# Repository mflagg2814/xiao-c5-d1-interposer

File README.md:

# XIAO ESP32-C5 to Wemos D1 mini interposer

> [!IMPORTANT]
> V1.0 hasn't been built or tested yet.\
> Use it at your own risk and without expectation of support.

A small interposer that lets a surface-mounted [Seeed Studio XIAO ESP32-C5](https://wiki.seeedstudio.com/xiao_esp32c5_getting_started/) stand in for a Wemos D1 mini (ESP8266). It breaks the XIAO out to the D1 mini's two 1×8 rows with the D1 mini's pin spacing, so it drops into D1 mini sockets and takes D1 mini shields.

It was built for the [AirGradient DIY Basic](https://www.airgradient.com/documentation/kb/kb-old-instructions-the-airgradient-diy-air-quality-sensor-basic-version-pcb-version-3-0). The pin map also aims to keep the board useful as a general D1 mini replacement.

Schematic: [c5-d1-interposer-schematic.pdf](c5-d1-interposer-schematic.pdf) (source: `c5-d1-interposer.kicad_sch`)

### AI disclosure

AI was used to generate this PCB with human guidance and revision. Provided without support.

## Fabrication

I had 3 of these fabbed 11/2026 at OSH Park for $4.05 including shipping. I went with 2oz copper, 0.8mm thickness.

## SHT3x: rewire VIN to 3.3 V

> [!WARNING]
> The SHT3x's VIN trace must be cut and rewired to 3.3 V before the XIAO goes in.

The AirGradient board powers the SHT3x module from 5 V. If that module has its own I2C pull-ups to VIN, SDA and SCL idle above the C5's 3.6 V absolute maximum. With 10k to 5 V on the module and the OLED shield's 4.7k to 3.3 V, the lines idle at about 3.84 V.

1. Cut the top-layer trace from the SHT3x footprint's VIN pad (the square pad) to the PMS5003 4-pin header's 5V pad. It runs about 6 mm straight across between the two pads, and feeds only that pad.
2. Wire the VIN pad to a 3V3 pad in the expansion grid, the 4×5 pad grid above the S8. Its columns, left to right, are 5V, 3V3, GND, SDA and SCL.

## Pin map

| D1 mini pin | XIAO pin           | C5 GPIO | Function on the C5                         | AirGradient use                                                       |
| ----------- | ------------------ | ------- | ------------------------------------------ | --------------------------------------------------------------------- |
| TX          | D6                 | GPIO11  | UART0 TX (U0TXD)                           | -                                                                     |
| RX          | D7                 | GPIO12  | UART0 RX (U0RXD)                           | -                                                                     |
| D1          | D5                 | GPIO24  | I2C SCL                                    | SCL: OLED, SHT3x                                                      |
| D2          | D4                 | GPIO23  | I2C SDA                                    | SDA: OLED, SHT3x                                                      |
| D3          | D10                | GPIO10  | GPIO / UART TX                             | ESP TX → SenseAir S8 RX                                               |
| D4          | D1                 | GPIO0   | GPIO / UART RX                             | SenseAir S8 TX → ESP RX                                               |
| D5          | D8                 | GPIO8   | GPIO / SPI SCK                             | PMS5003 TX → ESP RX                                                   |
| D6          | D9                 | GPIO9   | GPIO / SPI MISO                            | ESP TX → PMS5003 RX                                                   |
| D7          | D3                 | GPIO7   | GPIO / SPI MOSI (FSPID). **Strapping pin** | -                                                                     |
| D8          | D2                 | GPIO25  | GPIO / SPI CS. **Strapping pin**           | -                                                                     |
| A0          | D0                 | GPIO1   | ADC1_CH0                                   | -                                                                     |
| D0          | -                  | -       | Not connected                              | -                                                                     |
| RST         | EN pad (underside) | CHIP_PU | Chip reset, active low, through JP1        | -                                                                     |
| 3V3         | 3V3                | -       | XIAO 3.3 V output                          | OLED power, SHT3x power after the [rewire](#sht3x-rewire-vin-to-33-v) |
| 5V          | 5V                 | -       | XIAO VBUS (USB 5 V)                        | S8, PMS5003 power                                                     |
| G           | GND                | -       | Ground                                     | -                                                                     |

## Differences from a real D1 mini

Most D1 mini projects and shields should work, but check these first:

- **No onboard pull-ups or pull-downs.** The D1 mini has 10k pull-ups on D3 and D4 and a 10k pull-down on D8, because those are ESP8266 boot pins. This board has none of them. Use the C5's internal pull-ups or pull-downs in firmware if something depends on them.
- **No LED on D4.**
- **A0 is a raw ADC input**, 0–3.3 V straight into GPIO1. The D1 mini has a 220k/100k divider in front of the ESP8266's 1 V ADC, and some shields count on it. For example, the battery shield's A0 jumper adds a 130k series resistor sized for that divider, so here it would put up to 4.2 V on GPIO1 through 130k. Don't use it.
- **Only two hardware UARTs.** The C5 has UART0 and UART1 (its low-power UART isn't on the XIAO's pads). Any of them can be routed to any GPIO. If you use both for peripherals, as the AirGradient's SenseAir S8 and PMS5003 do, move the logger to the USB serial port. The ROM bootloader still prints its boot messages on the TX pin (GPIO11) at reset.
- **RST resets the C5**, as on a D1 mini. It's wired to the XIAO's EN pad through a solder-feed hole (see [Assembly](#assembly)). Software reboots (OTA, `restart`) don't pull EN low, so a shield that hangs its own chip's reset on RST only gets reset by a power cycle, the XIAO's reset button, or something pulling RST. To disconnect RST from EN, cut the trace between JP1's pads on the back, next to the solder-feed hole. Bridge the pads with solder to reconnect it.
- **Power:**
  - **5V** is tied straight to the XIAO's 5V pad, which is VBUS after the XIAO's USB load switch. You can power the board through the 5V pin instead of USB, but there's no diode between them: don't connect a 5 V supply to the 5V pin while USB is plugged in.
  - **3V3** is the XIAO's 3.3 V output, which sits behind a load switch on the XIAO. Treat it as an output only and don't power the board through it.

## Assembly

1. Optionally, put a thin layer of thermal paste on the bare thermal pad.
2. Solder the XIAO flat on the top side, with its USB-C port at the edge marked **USB-C this end** on the back silkscreen. Solder all 14 castellated edges first.
3. From the back, feed solder into the hole near the USB end. It sits under the XIAO's EN test pad (underside pad 17) and connects it to the RST pin.

# Sources

- **XIAO symbol and footprint:** derived from Seeed Studio's [OPL KiCad library, XIAO Family](https://github.com/Seeed-Studio/OPL_Kicad_Library/tree/master/XIAO%20Family). Underside pad positions and functions were checked against Seeed's [XIAO ESP32-C5 V1.1 schematic and PCB](https://wiki.seeedstudio.com/xiao_esp32c5_getting_started/).
- **XIAO 3D model:** not included, because GrabCAD models can't be redistributed. Download "[Seeed Studio XIAO ESP32-C5](https://grabcad.com/library/seeed-studio-xiao-esp32-c5-1)" from GrabCAD and save it as `lib/c5d1.3dshapes/seeed-studio-xiao-esp32c5.step` to see the XIAO in KiCad's 3D viewer.

# License

- The board design is under the [MIT License](LICENSE).
- The XIAO symbol and footprint (`lib/c5d1.kicad_sym`, `lib/c5d1.pretty/`) are derived from Seeed Studio's OPL KiCad library and stay under [CC BY-SA 4.0](lib/LICENSE.md), including the copies KiCad embeds in the schematic and board files.

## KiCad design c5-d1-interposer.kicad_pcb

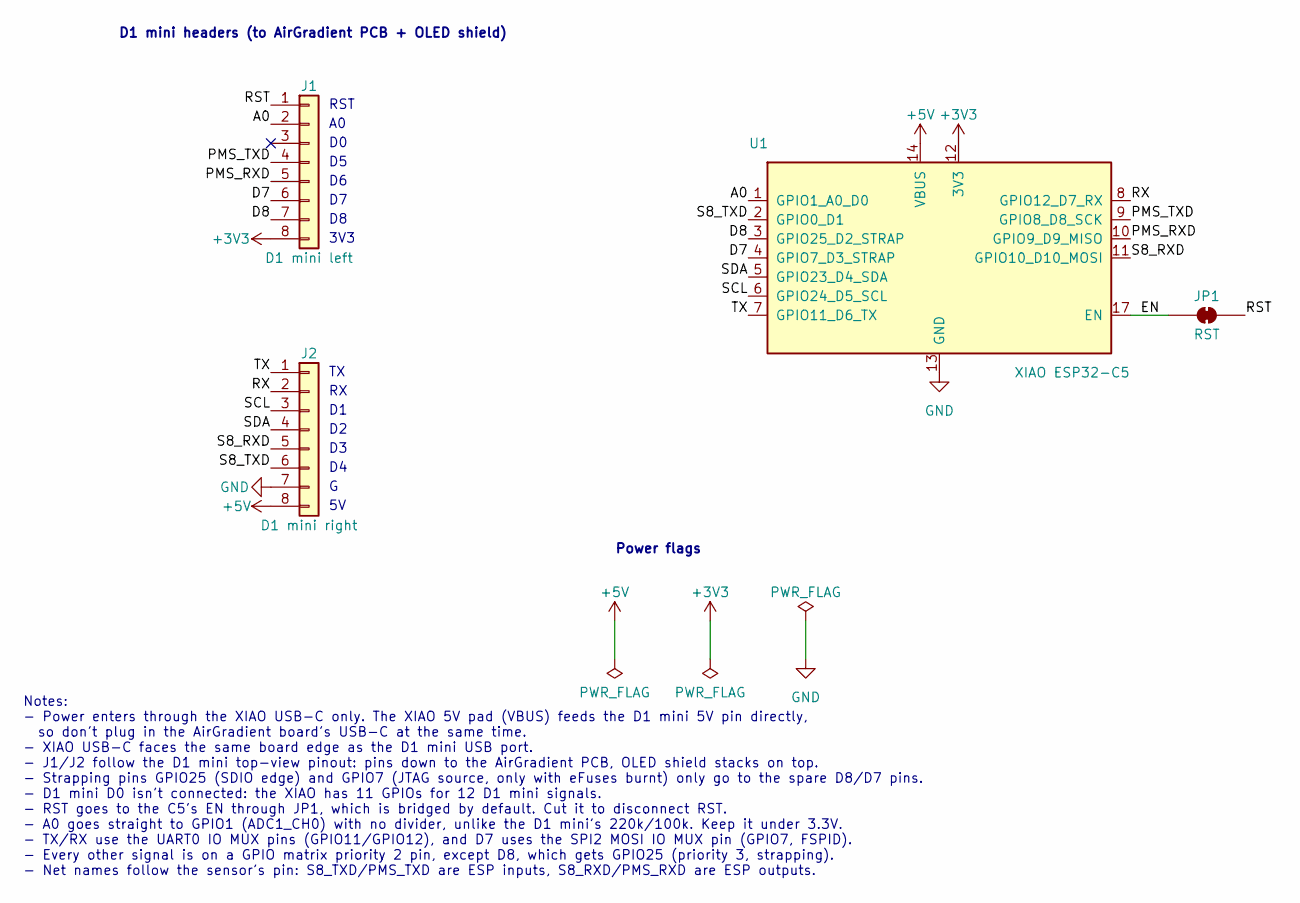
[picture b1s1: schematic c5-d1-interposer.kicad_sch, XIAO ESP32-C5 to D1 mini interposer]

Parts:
J1: D1 mini left; PinHeader_1x08_P2.54mm_Vertical_Round
J2: D1 mini right; PinHeader_1x08_P2.54mm_Vertical_Round
JP1: RST; SolderJumper-2_P1.3mm_Bridged_RoundedPad1.0x1.5mm
U1: XIAO ESP32-C5; XIAO-ESP32-C5-SMD

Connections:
+3V3: J1.8, U1.12 (3V3)
+5V: J2.8, U1.14 (VBUS)
/A0: J1.2, U1.1 (GPIO1_A0_D0)
/D7: J1.6, U1.4 (GPIO7_D3_STRAP)
/D8: J1.7, U1.3 (GPIO25_D2_STRAP)
/EN: JP1.1 (A), U1.17 (EN)
/PMS_RXD: J1.5, U1.10 (GPIO9_D9_MISO)
/PMS_TXD: J1.4, U1.9 (GPIO8_D8_SCK)
/RST: J1.1, JP1.2 (B)
/RX: J2.2, U1.8 (GPIO12_D7_RX)
/S8_RXD: J2.5, U1.11 (GPIO10_D10_MOSI)
/S8_TXD: J2.6, U1.2 (GPIO0_D1)
/SCL: J2.3, U1.6 (GPIO24_D5_SCL)
/SDA: J2.4, U1.5 (GPIO23_D4_SDA)
/TX: J2.1, U1.7 (GPIO11_D6_TX)
GND: J2.7, U1.13 (GND)

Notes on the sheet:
RST
3V3
Power flags
Notes: - Power enters through the XIAO USB-C only. The XIAO 5V pad (VBUS) feeds the D1 mini 5V pin directly, so don't plug in the AirGradient board's USB-C at the same time. - XIAO USB-C faces the same board edge as the D1 mini USB port. - J1/J2 follow the D1 mini top-view pinout: pins down to the 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
D1 mini headers (to AirGradient PCB + OLED shield)

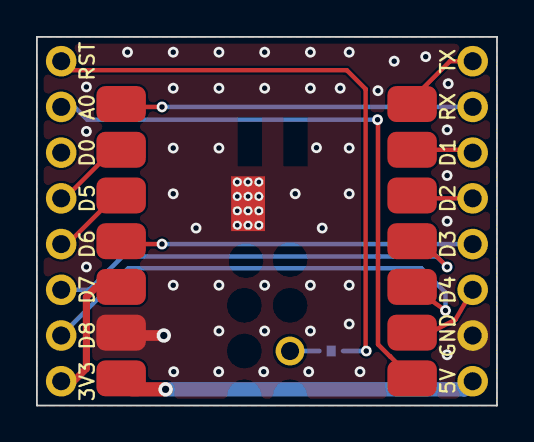
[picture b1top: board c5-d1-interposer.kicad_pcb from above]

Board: 2 copper layers, 25.6 x 20.5 mm, 4 parts (1 on the bottom side), 16 nets.
